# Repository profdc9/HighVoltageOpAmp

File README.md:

# High Voltage Discrete Op Amp

This is a discrete op-amp made from MMBT5551/MMBT5401 that can be used up to +/- 75V rail voltage.

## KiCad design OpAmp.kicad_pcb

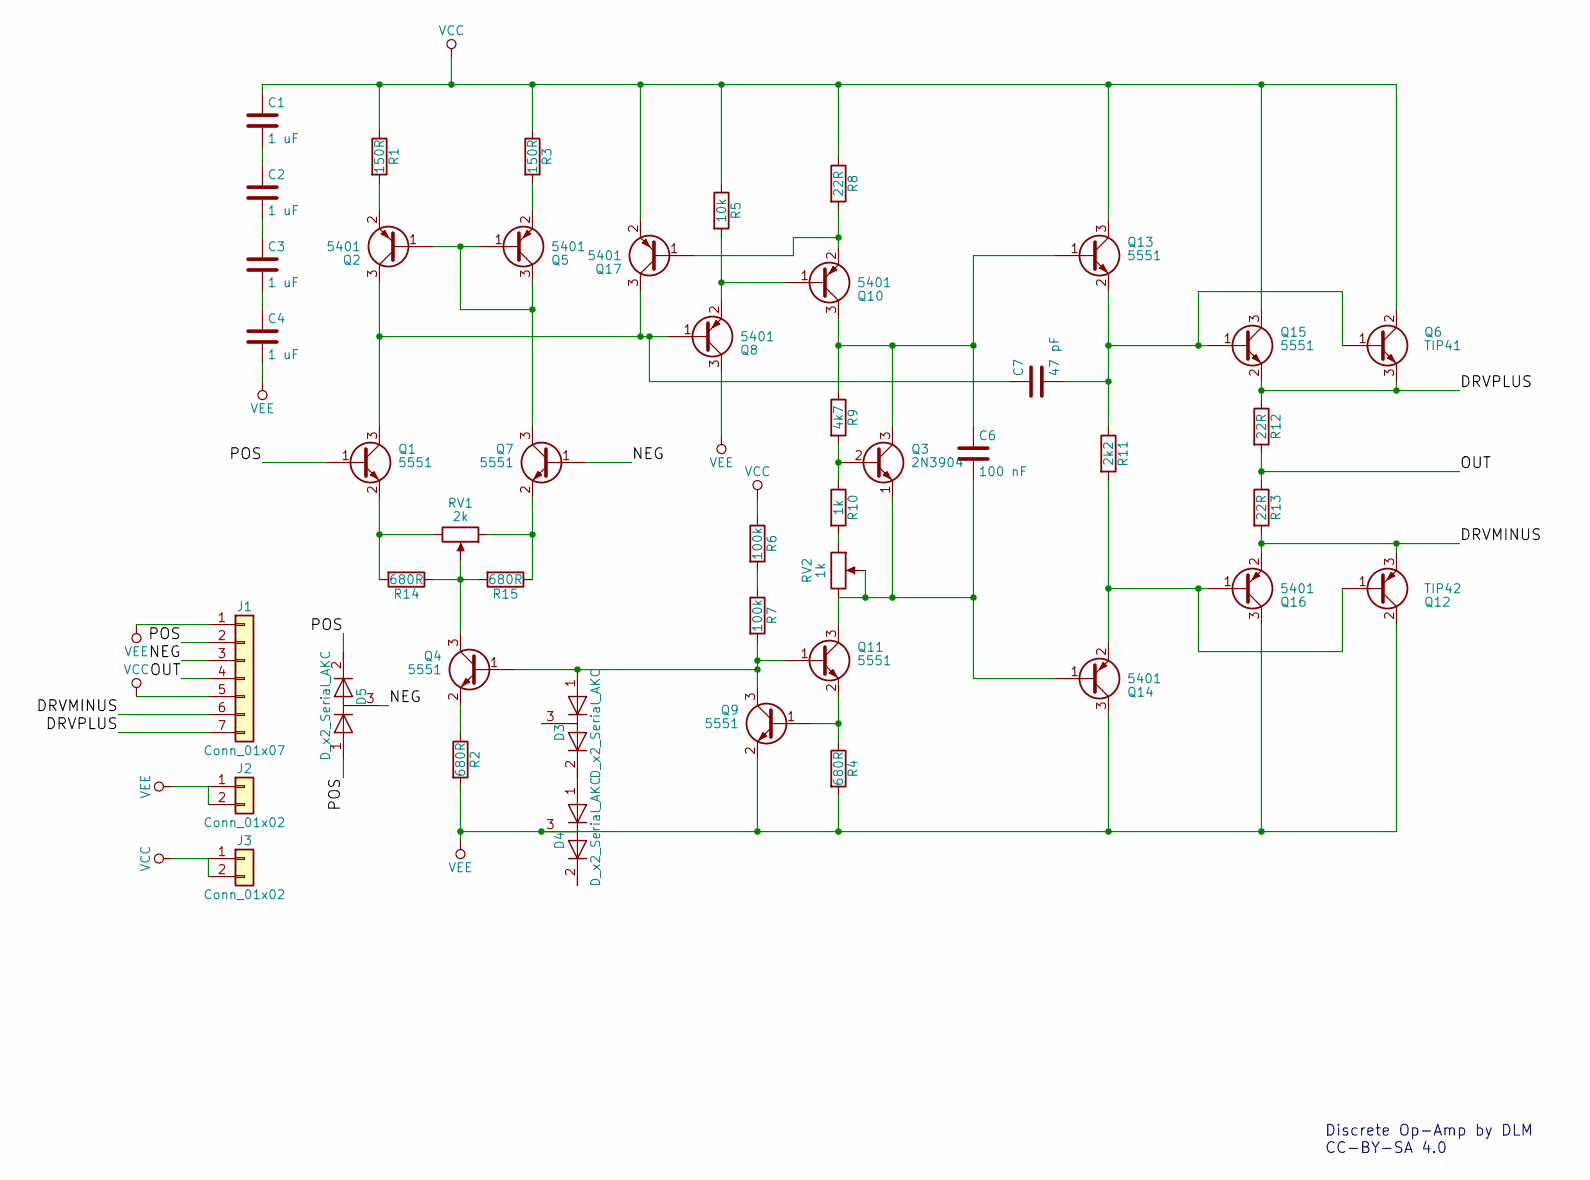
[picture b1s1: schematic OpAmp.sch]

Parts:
C1, C2, C3, C4: 1 uF; C_0805_HandSoldering; LCSC C28323
C6: 100 nF; C_0805_HandSoldering; LCSC C49678
C7: 47 pF; C_0805_HandSoldering; LCSC C14857
D3, D4, D5: D_x2_Serial_AKC; SOT-23; LCSC C2500
J1: Conn_01x07; Pin_Header_Straight_1x07_Pitch2.54mm
J2, J3: Conn_01x02; Pin_Header_Straight_1x02_Pitch2.54mm
Q1, Q4, Q7, Q9, Q11, Q13, Q15: 5551; SOT-23; LCSC C2145
Q2, Q5, Q8, Q10, Q14, Q16, Q17: 5401; SOT-23; LCSC C8326
Q3: 2N3904; TO-92_Inline_Wide
Q6: TIP41; TO-220-3_Vertical
Q12: TIP42; TO-220-3_Vertical
R1, R3: 150R; R_0805_HandSoldering; LCSC C17471
R2, R4, R14, R15: 680R; R_0805_HandSoldering; LCSC C17798
R5: 10k; R_0805_HandSoldering; LCSC C17414
R6, R7: 100k; R_0805_HandSoldering; LCSC C17407
R8: 22R; R_0805_HandSoldering; LCSC C17561
R9: 4k7; R_0805_HandSoldering; LCSC C17673
R10: 1k; R_0805_HandSoldering; LCSC C17513
R11: 2k2; R_0805_HandSoldering; LCSC C17520
R12, R13: 22R; R_1206_HandSoldering; LCSC C17958
RV1: 2k; Potentiometer_Trimmer_Bourns_3296W
RV2: 1k; Potentiometer_Trimmer_Bourns_3296W

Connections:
/DRVMINUS: J1.6, Q12.3 (E), Q16.2 (E), R13.2
/DRVPLUS: J1.7, Q6.3 (E), Q15.2 (E), R12.1
/NEG: D5.3 (common), J1.3, Q7.1 (B)
/OUT: J1.4, R12.2, R13.1
/POS: D5.1 (A), D5.2 (K), J1.2, Q1.1 (B)
unnamed: C1.2, C2.1
unnamed: C2.2, C3.1
unnamed: C3.2, C4.1
unnamed: C6.1, Q3.3 (C), Q10.3 (C), Q13.1 (B), R9.1
unnamed: C6.2, Q3.1 (E), Q11.3 (C), Q14.1 (B), RV2.2, RV2.3
unnamed: C7.1, Q1.3 (C), Q2.3 (C), Q8.1 (B), Q17.3 (C)
unnamed: C7.2, Q6.1 (B), Q13.2 (E), Q15.1 (B), R11.1
unnamed: D3.1 (A), Q4.1 (B), Q9.3 (C), Q11.1 (B), R7.2
unnamed: D3.2 (K), D4.1 (A)
unnamed: Q1.2 (E), R14.2, RV1.3
unnamed: Q2.1 (B), Q5.1 (B), Q5.3 (C), Q7.3 (C)
unnamed: Q2.2 (E), R1.2
unnamed: Q3.2 (B), R9.2, R10.1
unnamed: Q4.2 (E), R2.1
unnamed: Q4.3 (C), R14.1, R15.2, RV1.2
unnamed: Q5.2 (E), R3.2
unnamed: Q7.2 (E), R15.1, RV1.1
unnamed: Q8.2 (E), Q10.1 (B), R5.2
unnamed: Q10.2 (E), Q17.1 (B), R8.2
unnamed: Q9.1 (B), Q11.2 (E), R4.1
unnamed: Q12.1 (B), Q14.2 (E), Q16.1 (B), R11.2
unnamed: R6.2, R7.1
unnamed: R10.2, RV2.1
VCC: C1.1, J1.5, J3.1, J3.2, Q6.2 (C), Q13.3 (C), Q15.3 (C), Q17.2 (E), R1.1, R3.1, R5.1, R6.1, R8.1
VEE: C4.2, D4.3 (common), J1.1, J2.1, J2.2, Q8.3 (C), Q9.2 (E), Q12.2 (C), Q14.3 (C), Q16.3 (C), R2.2, R4.2

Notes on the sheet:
Discrete Op-Amp by DLM CC-BY-SA 4.0

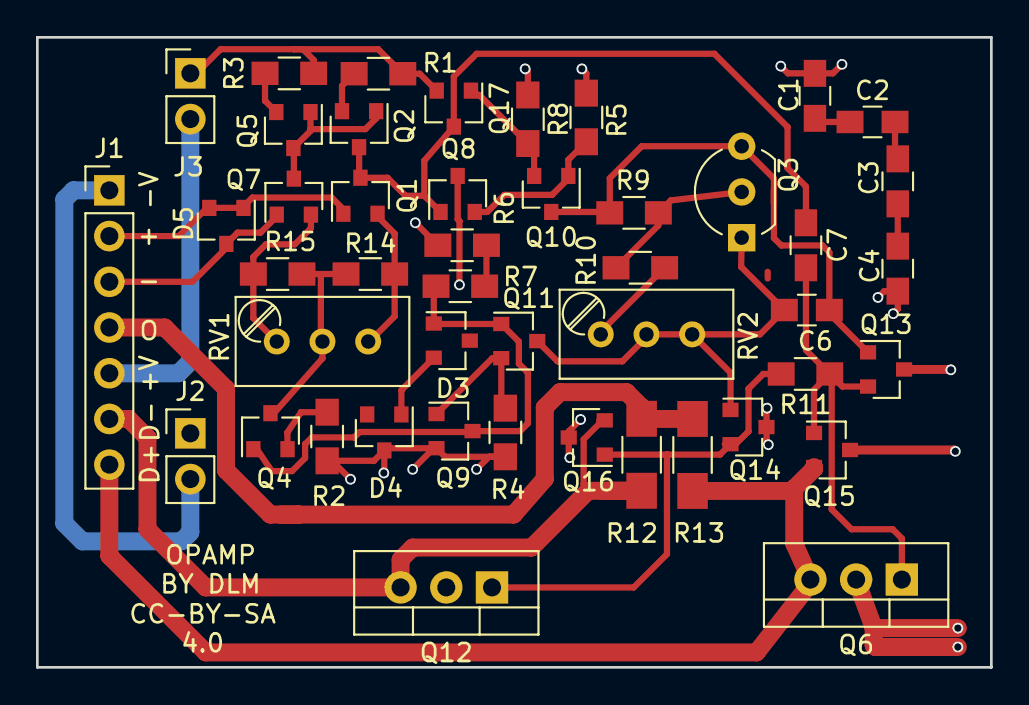
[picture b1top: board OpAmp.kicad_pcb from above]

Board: 2 copper layers, 53.0 x 35.0 mm, 46 parts (0 on the bottom side), 30 nets.

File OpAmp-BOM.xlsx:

Comment | Designator | Footprint | LCSC
1 uF | C1,C2,C3,C4 | Capacitors_SMD:C_0805_HandSoldering | C28323
100 nF | C6 | Capacitors_SMD:C_0805_HandSoldering | C49678
47 pF | C7 | Capacitors_SMD:C_0805_HandSoldering | C14857
D_x2_Serial_AKC | D3,D4,D5 | TO_SOT_Packages_SMD:SOT-23 | C2500
Conn_01x07 | J1 | Pin_Headers:Pin_Header_Straight_1x07_Pitch2.54mm
Conn_01x02 | J2,J3 | Pin_Headers:Pin_Header_Straight_1x02_Pitch2.54mm
5551 | Q1,Q4,Q7,Q9,Q11,Q13,Q15 | TO_SOT_Packages_SMD:SOT-23 | C2145
TIP42 | Q12 | TO_SOT_Packages_THT:TO-220-3_Vertical
2N3904 | Q3 | TO_SOT_Packages_THT:TO-92_Inline_Wide
TIP41 | Q6 | TO_SOT_Packages_THT:TO-220-3_Vertical
5401 | Q2,Q5,Q8,Q10,Q14,Q16,Q17 | TO_SOT_Packages_SMD:SOT-23 | C8326
1k | R10 | Resistors_SMD:R_0805_HandSoldering | C17513
2k2 | R11 | Resistors_SMD:R_0805_HandSoldering | C17520
22R | R12,R13 | Resistors_SMD:R_1206_HandSoldering | C17958
680R | R2,R4,R14,R15 | Resistors_SMD:R_0805_HandSoldering | C17798
150R | R1,R3 | Resistors_SMD:R_0805_HandSoldering | C17471
10k | R5 | Resistors_SMD:R_0805_HandSoldering | C17414
100k | R6,R7 | Resistors_SMD:R_0805_HandSoldering | C17407
22R | R8 | Resistors_SMD:R_0805_HandSoldering | C17561
4k7 | R9 | Resistors_SMD:R_0805_HandSoldering | C17673
2k | RV1 | Potentiometers:Potentiometer_Trimmer_Bourns_3296W
1k | RV2 | Potentiometers:Potentiometer_Trimmer_Bourns_3296W

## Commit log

2021-04-13 JLCPCB order 2021-04-11
2021-05-19 Added partial outputs
2021-05-23 Add spot for power transistors
2021-05-28 JLCPCB manufacturing
2023-01-10 Added VAS safety transistor
2023-01-10 Updated schematic pdf
2023-01-10 Fixed pinout on TIP42
